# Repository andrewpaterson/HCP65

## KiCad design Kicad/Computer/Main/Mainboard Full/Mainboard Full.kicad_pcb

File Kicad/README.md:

# Kicad

The HCP65's circuit boards, drawn in KiCad 8, and the libraries they are drawn with.  The schematics are a source
of the website's hardware pages (`HCP65-Emulator/HCP65Lib/Docs/hcp65`): what a page says about a board is made from
or checked against its schematic (`Website/DocsPlan.txt` I).

| Folder | Has |
|---|---|
| `Computer` | The computer's boards, by what they do: Main, Memory, Audio, Video, the device boards, and `Component Boards`, the small boards the others are built from. |
| `Boards` | Blank boards (`Blank`) and pin boards (`Pins`) of each size of socket, to start a board from. |
| `Pico`, `Programmers`, `Tester`, `Speed`, `Keypad` | Test, programming and other boards beside the computer. |
| `X65C64` | The 65C64 drawn as a part: its schematic and board. |
| `Old` | Boards no longer built, kept to look back at. |
| `Symbols`, `HCP65_Parts.pretty` | The symbol libraries (one a maker, and `HCP65.kicad_sym`, a symbol a board) and the footprints of the boards and sockets. |
| `SamacSys_Parts.pretty`, `SamacSys_Parts.3dshapes` | Footprints and 3D models of bought parts. |

A board's `<board> Faults.txt` (and `Symbols/Symbol Faults.txt`) lists what a review found wrong with it.  Export
from a copy of a project, not the project itself: `kicad-cli` rewrites the `.kicad_prl` beside every schematic it
reads.

| Files | Are | From |
|---|---|---|
| `**/*.kicad_sch`, `**/*.kicad_pcb`, `**/*.kicad_pro`, `*.kicad_wks`, `**/*.round-tracks-config`, `**/*.par`, `**/*.frb`, `**/sym-lib-table`, `Old/**/*.sch`, `Old/**/*.pro`, `Old/**/*.dcm` | Source | Drawn in KiCad 8 (`Old`'s `.sch`, `.pro` and `.dcm` in KiCad 5); the round tracks plugin's settings and Freerouting's files. |
| `**/*.txt` | Source | Notes: each review's faults, pin lists. |
| `Symbols/*.kicad_sym`, `HCP65_Parts.pretty/*.kicad_mod` | Source | Drawn and kept here (the makers' symbols were begun from SamacSys's, and corrected as `Symbols/Symbol Faults.txt` says). |
| `SamacSys_Parts.pretty/*.kicad_mod`, `SamacSys_Parts.3dshapes/*` | Third-party | SamacSys's Component Search Engine: each part's footprint and 3D model as its Library Loader downloaded it. |
| `**/*.g[bt][losp]`, `**/*.gm1`, `**/*.gbr`, `**/*.gbrjob`, `**/*.drl` | Generated | A board's Gerber and drill files, plotted from its `.kicad_pcb` by KiCad 8's Pcbnew (File, Fabrication Outputs: Gerbers, then Drill Files; `kicad-cli pcb export gerbers` and `kicad-cli pcb export drill` make the same) into a folder named for the board beside it. |
| `Boards/**/*.wrl`, `Computer/**/*.wrl`, `Old/**/*.wrl`, `Pico/**/*.wrl`, `Tester/**/*.wrl` | Generated | A board's 3D model, exported from its `.kicad_pcb` by Pcbnew (File, Export, VRML; `kicad-cli pcb export vrml`). |
| `Old/**/*.step` | Generated | A board's 3D model, exported from its `.kicad_pcb` by Pcbnew (File, Export, STEP; `kicad-cli pcb export step`). |
| `**/*.cad` | Generated | A board in GenCAD, exported from its `.kicad_pcb` by Pcbnew (File, Export, GenCAD). |
| `Old/**/*.net` | Generated | A schematic's netlist, exported by Eeschema (File, Export, Netlist; `kicad-cli sch export netlist`). |
| `Keypad/Fabrication/*.7z` | Generated | The Keypad's Gerber and drill files beside it, packed to send to the board maker. |

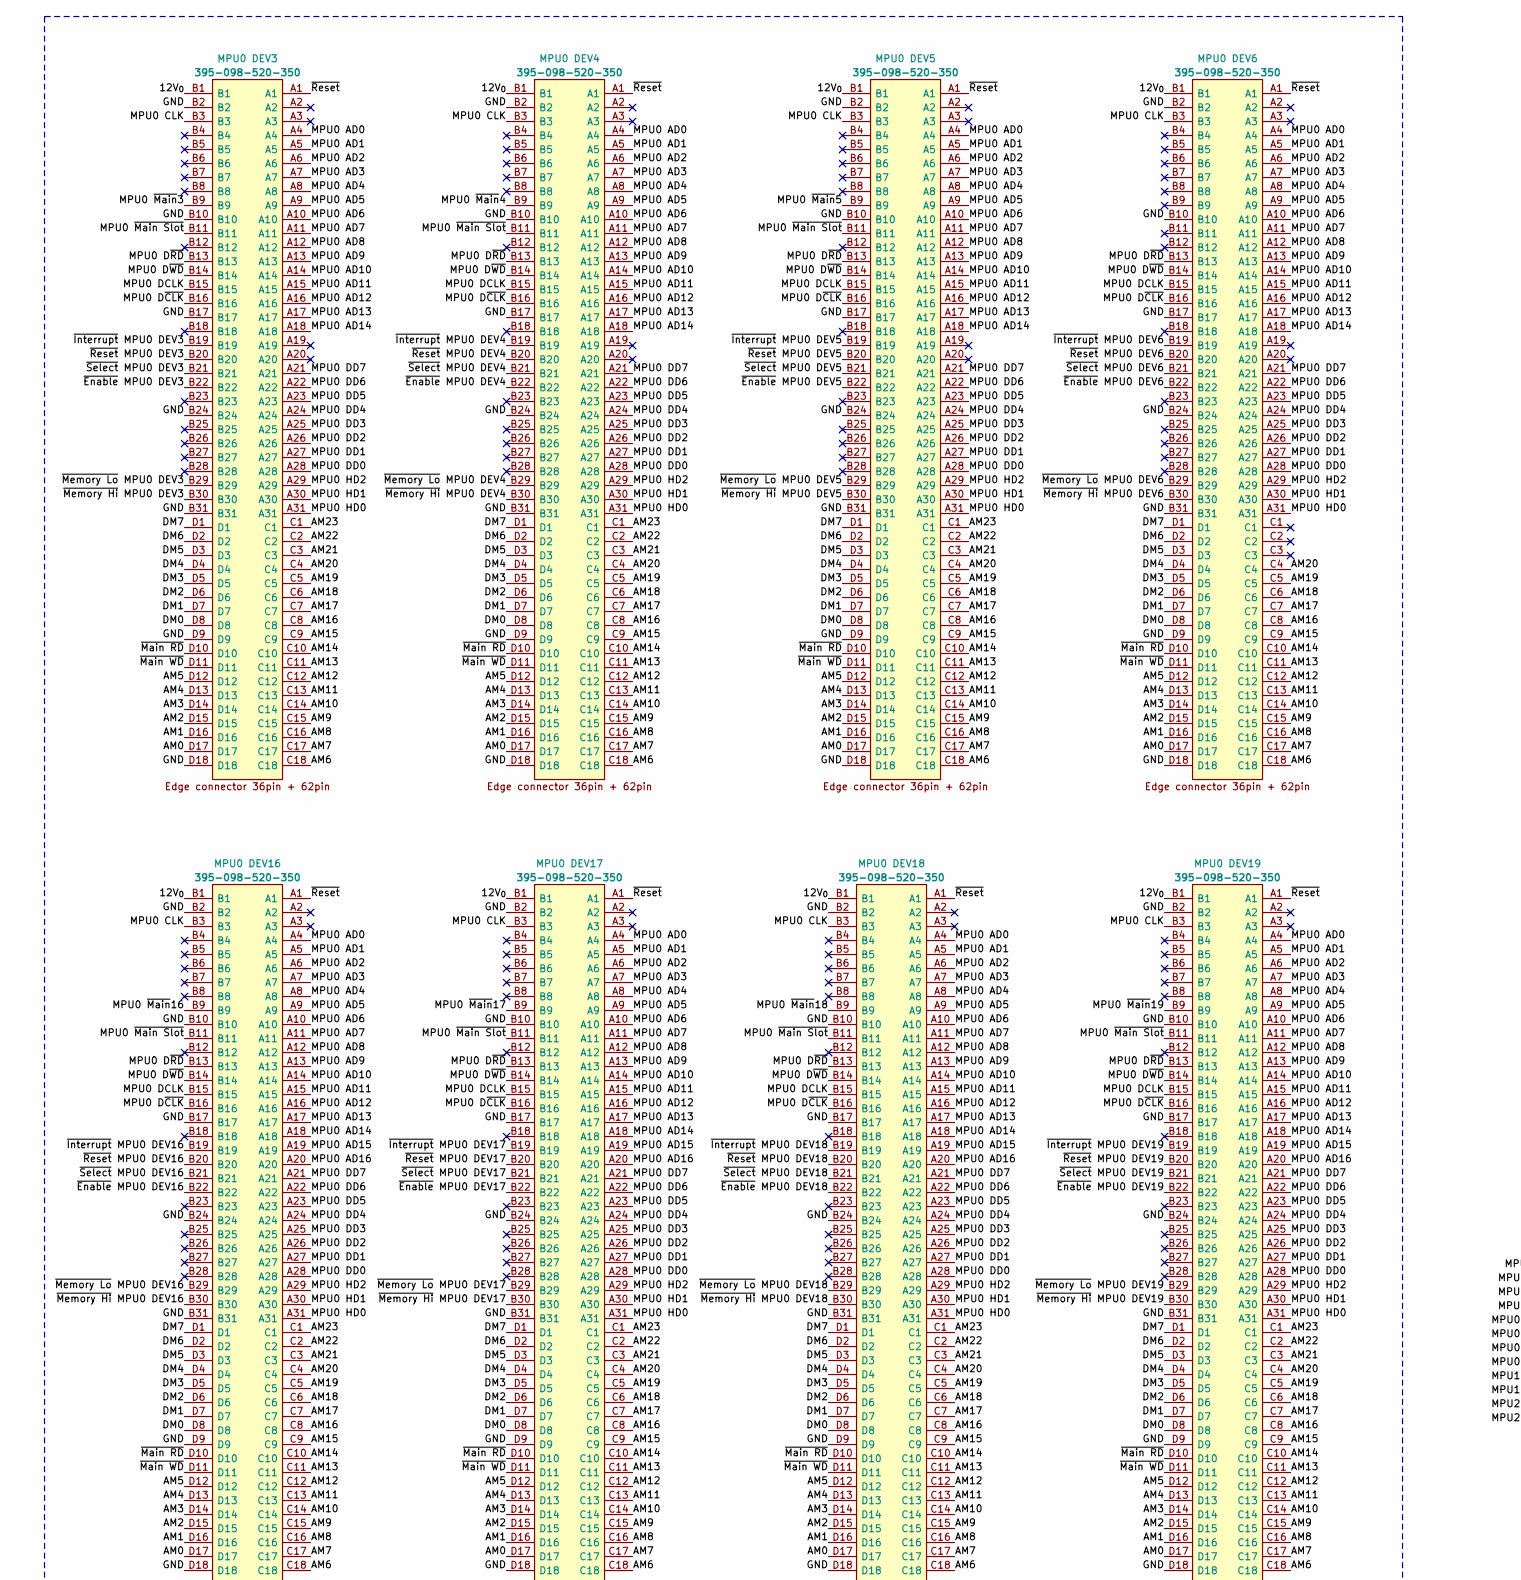
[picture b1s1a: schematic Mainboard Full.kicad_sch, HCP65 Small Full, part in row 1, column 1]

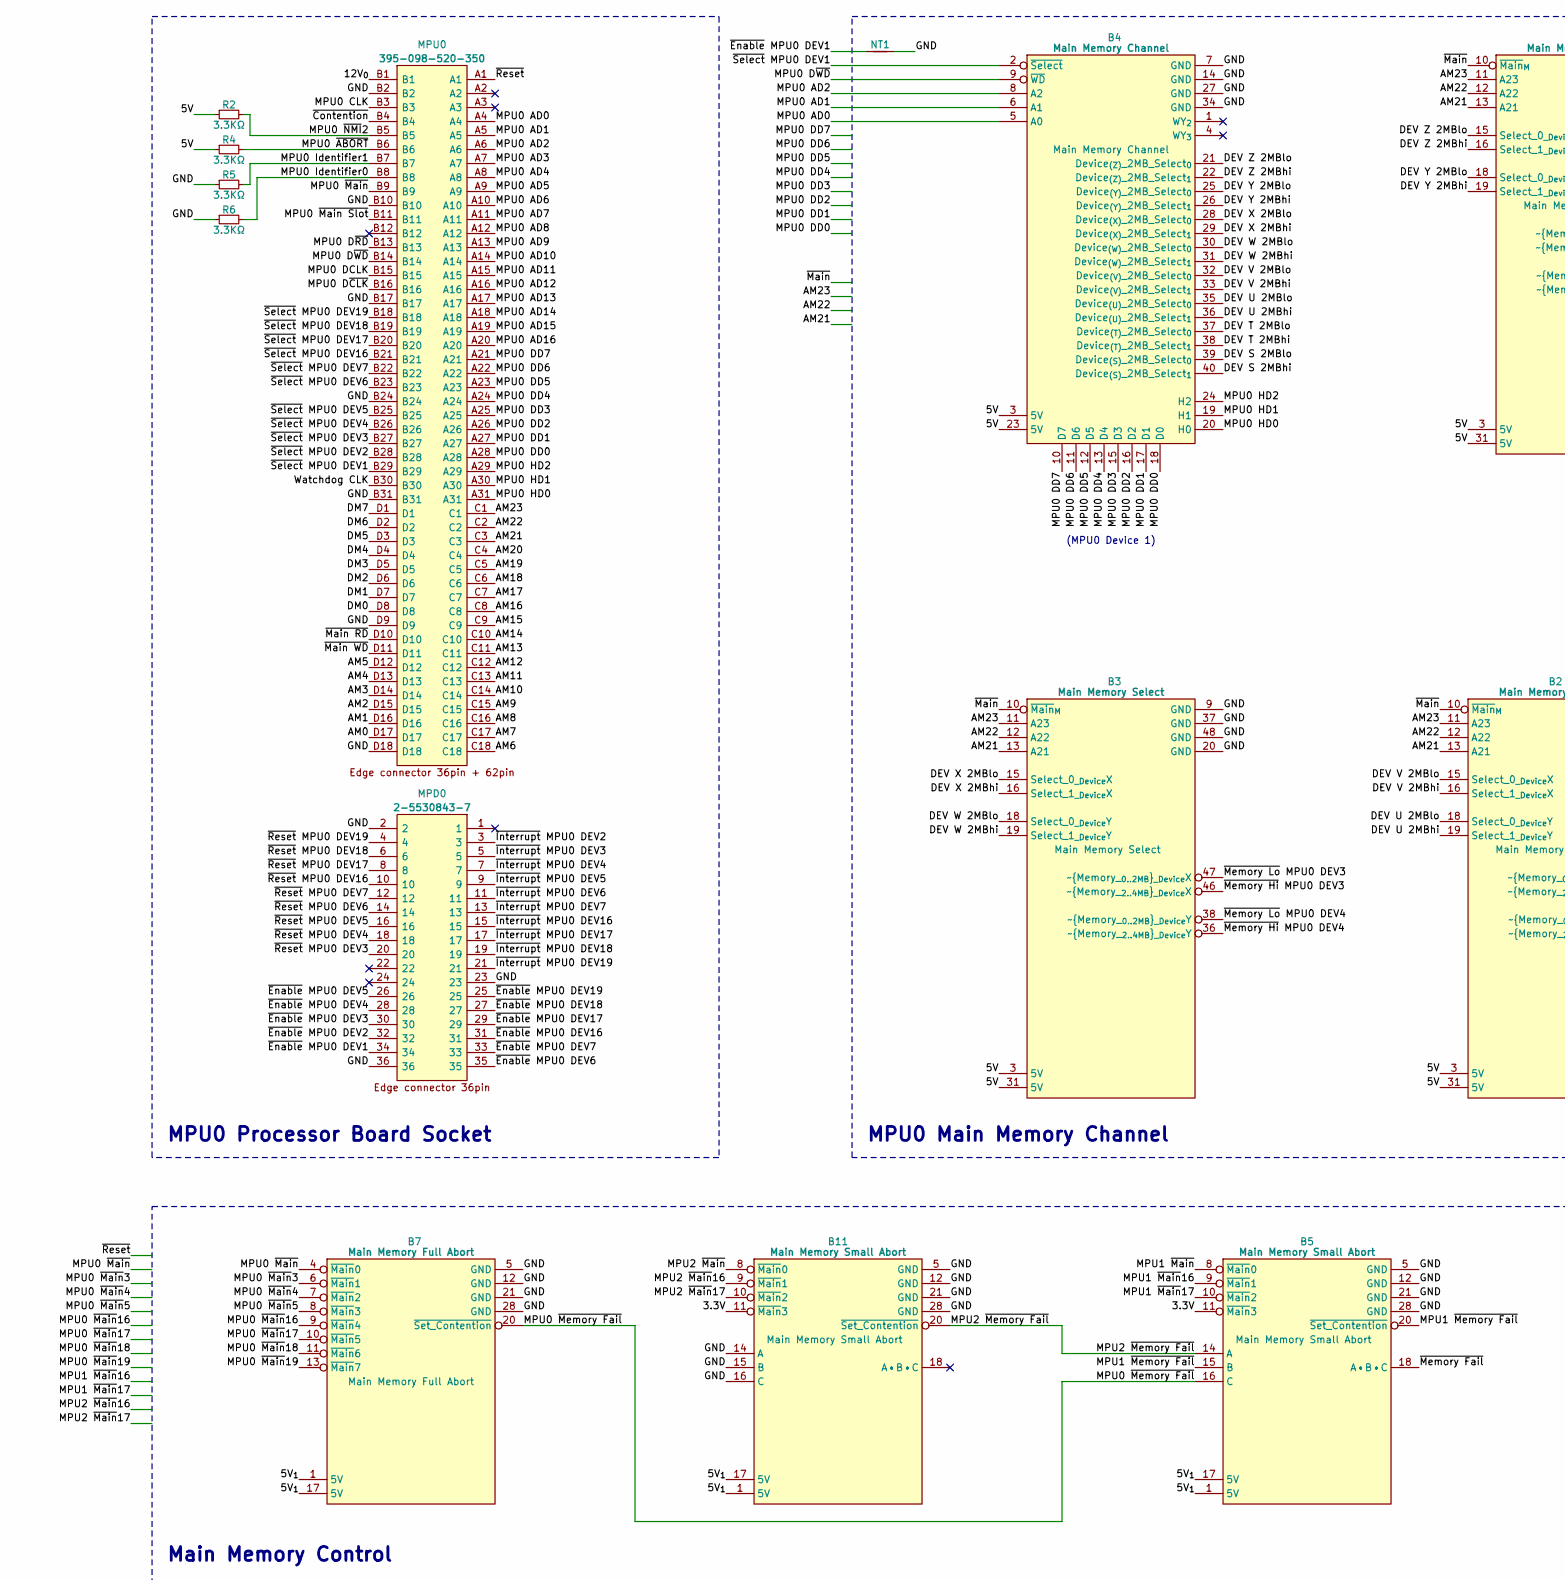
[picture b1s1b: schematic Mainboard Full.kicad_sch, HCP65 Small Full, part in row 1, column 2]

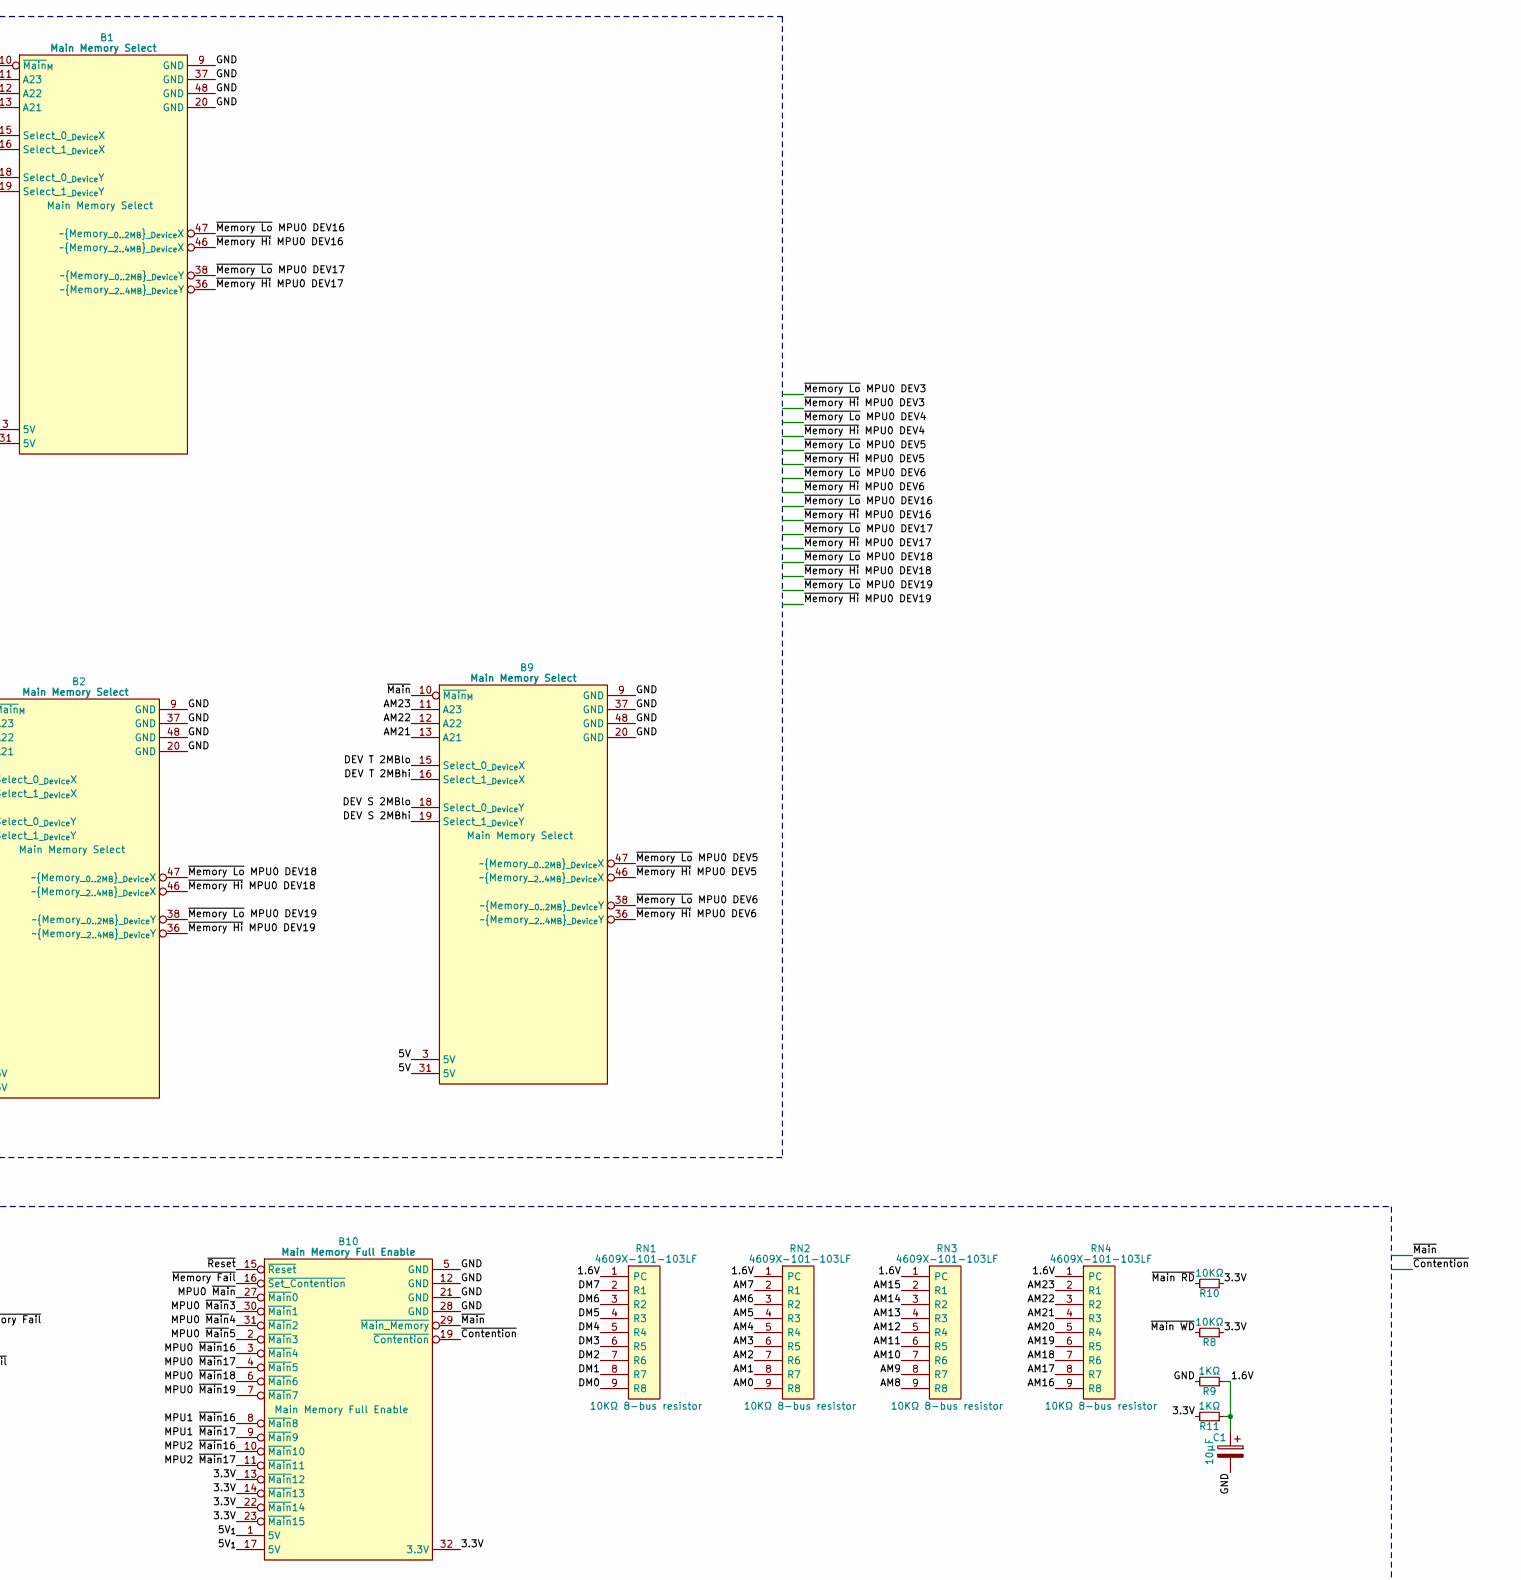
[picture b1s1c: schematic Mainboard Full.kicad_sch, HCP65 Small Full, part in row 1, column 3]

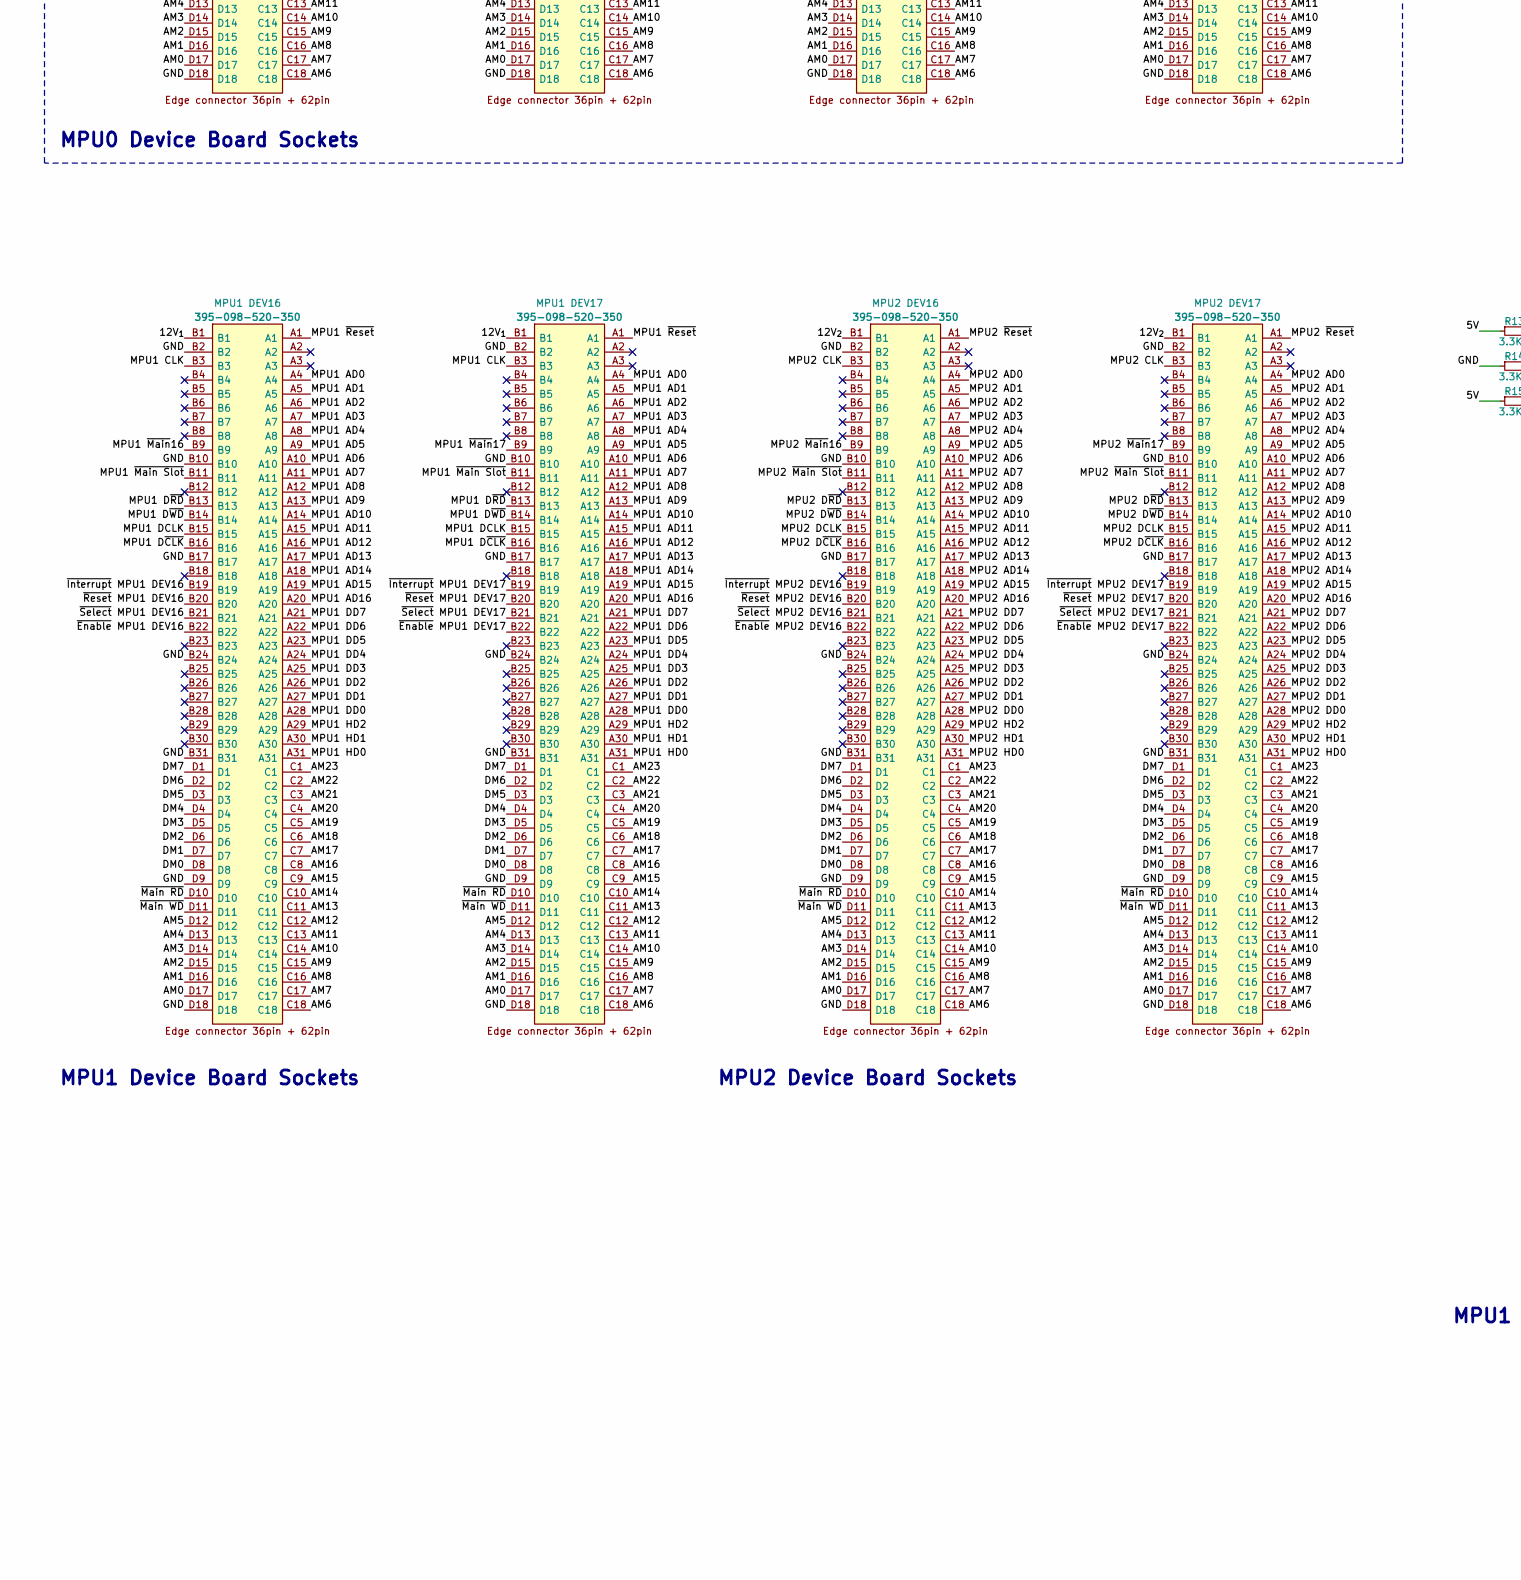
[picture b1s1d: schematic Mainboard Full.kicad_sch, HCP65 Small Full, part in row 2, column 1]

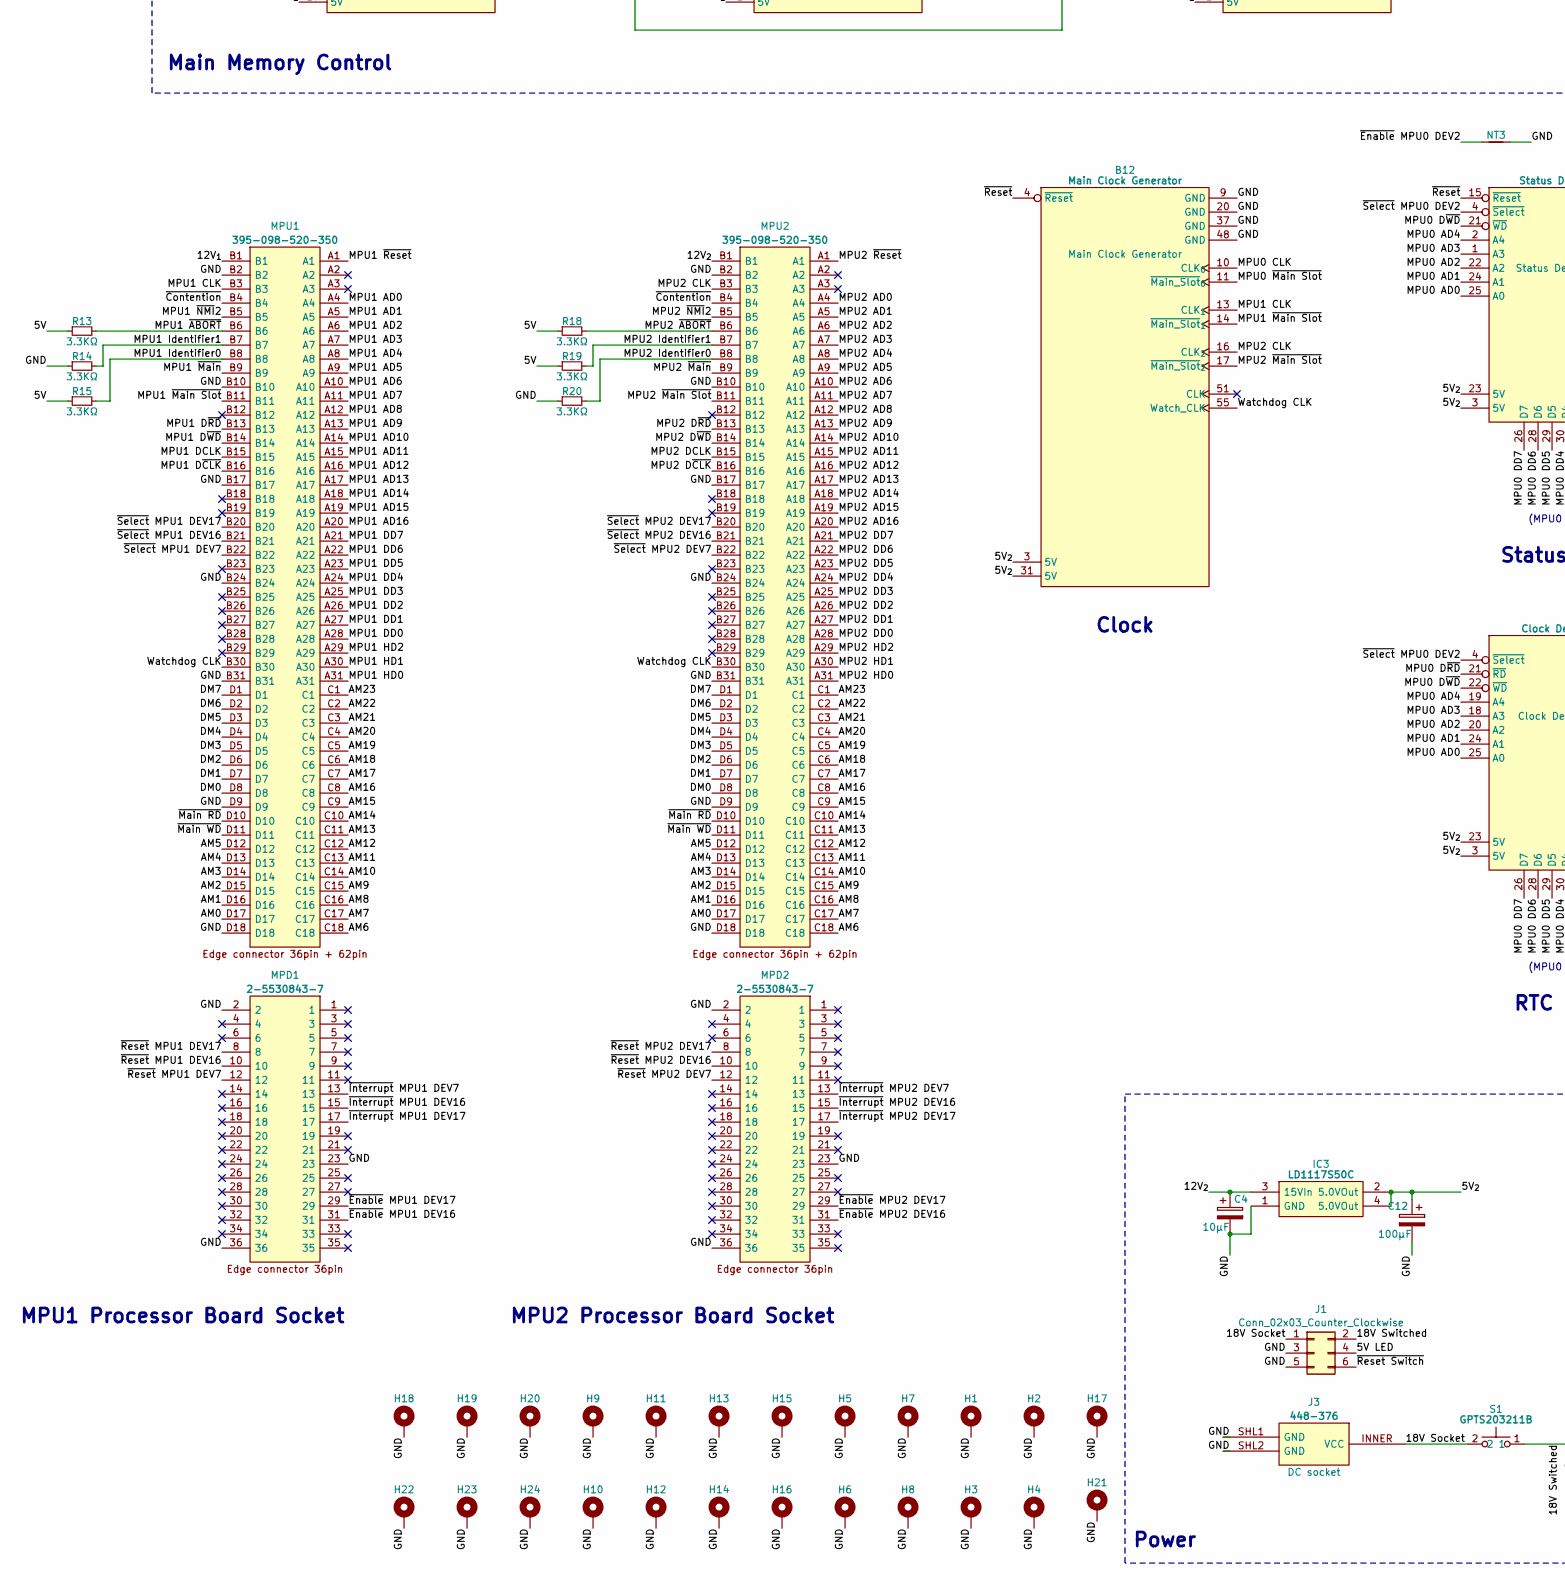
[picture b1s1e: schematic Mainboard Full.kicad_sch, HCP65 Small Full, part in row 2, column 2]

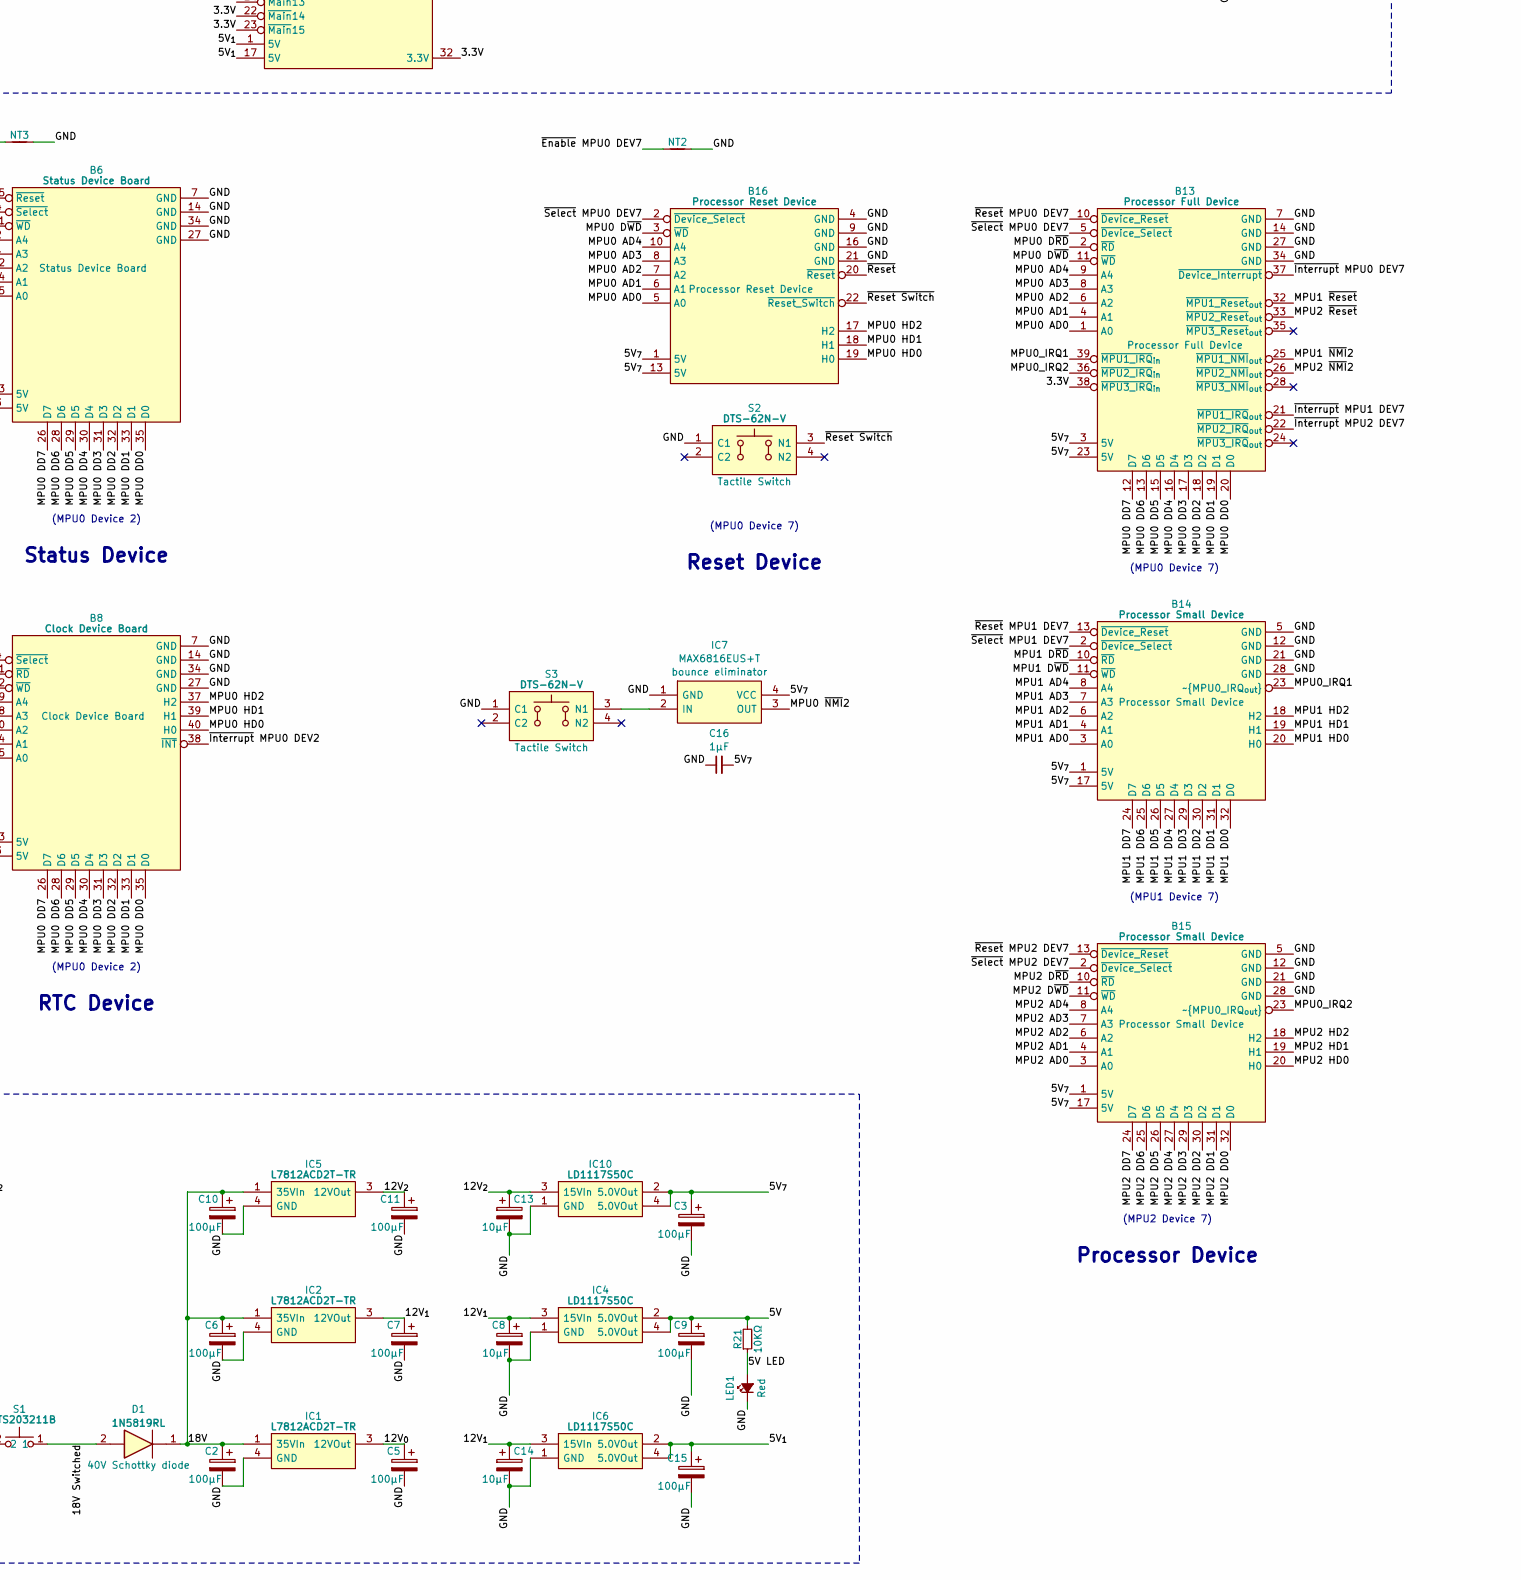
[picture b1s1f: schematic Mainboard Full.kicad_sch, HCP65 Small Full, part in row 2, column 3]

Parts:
B1, B2, B3, B9: Main Memory Select; HCP65_Main_Memory_Select
B4: Main Memory Channel; HCP65_Main_Memory_Channel
B5, B11: Main Memory Small Abort; HCP65_Main_Memory_Small_Abort
B6: Status Device Board; HCP65_Status_Device_Board
B7: Main Memory Full Abort; HCP65_Main_Memory_Full_Abort
B8: Clock Device Board; HCP65_Clock_Device_Board
B10: Main Memory Full Enable; HCP65_Main_Memory_Full_Enable
B12: Main Clock Generator; HCP65_Clock_Generator
B13: Processor Full Device; HCP65_Processor_Full_Device
B14, B15: Processor Small Device; HCP65_Processor_Small_Device
B16: Processor Reset Device; HCP65_Processor_Reset_Device
C1, C4, C8, C13, C14: 10μF; CP_Radial_D4.0mm_P2.00mm
C2, C3, C5, C6, C7, C9, C10, C11, C12, C15: 100μF; CP_Radial_D6.3mm_P2.50mm
C16: 1μF; C_0805
D1: 1N5819RL; DIOAD1414W86L464D238; Manufacturer_Part_Number 1N5819RL; Mouser Part Number 511-1N5819-TR
H1, H2, H3, H4, H5, H6, H7, H8, H9, H10, H11, H12, H13, H14, H15, H16, H17, H18, H19, H20, H21, H22, H23, H24: MountingHole_Pad; HCP65_MountingHole_M3_
IC1, IC2, IC5: L7812ACD2T-TR; TO254P1542X460-3N; Manufacturer_Part_Number L7812ACD2T-TR
IC3, IC4, IC6, IC10: LD1117S50C; LD1117S33C; Manufacturer_Part_Number LD1117S50C
IC7: MAX6816EUS+T; MAX812REUST; Manufacturer_Part_Number MAX6816EUS+T; Mouser Part Number 700-MAX6816EUST
J1: Conn_02x03_Counter_Clockwise; PinHeader_2x03_P2.54mm_Vertical
J3: 448-376; 448376; Manufacturer_Part_Number 448-376
LED1: Red; LED_D5.0mm
MPD0, MPD1, MPD2: 2-5530843-7; 255308437; Manufacturer_Part_Number 2-5530843-7; Mouser Part Number 571-2-5530843-7
MPU0, MPU0 DEV3, MPU0 DEV4, MPU0 DEV5, MPU0 DEV6, MPU0 DEV16, MPU0 DEV17, MPU0 DEV18, MPU0 DEV19, MPU1, MPU1 DEV16, MPU1 DEV17, MPU2, MPU2 DEV16, MPU2 DEV17: 395-098-520-350; 395098520350; Manufacturer_Part_Number 395-098-520-350; Mouser Part Number 587-395-098-520-350
NT1, NT2, NT3: NetTie; NetTie-2_SMD_Pad0.5mm
R2, R4, R5, R6, R13, R14, R15, R18, R19, R20: 3.3KΩ; R_0805
R8, R10, R21: 10KΩ; R_0805
R9, R11: 1KΩ; R_0805
RN1, RN2, RN3, RN4: 4609X-101-103LF; 4609X
S1: GPTS203211B; Manufacturer_Part_Number GPTS203211B; Mouser Part Number 629-GPTS203211B
S2, S3: DTS-62N-V; DTS62NV; Manufacturer_Part_Number DTS-62N-V; Mouser Part Number 113-DTS-62N-V

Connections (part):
/1.6V: C1.1, R9.1, R11.1, RN1.1 (PC), RN2.1 (PC), RN3.1 (PC), RN4.1 (PC)
/3.3V: B5.11 (~Main3), B10.13 (~Main12), B10.14 (~Main13), B10.22 (~Main14), B10.23 (~Main15), B10.32 (3.3V), B11.11 (~Main3), B13.38 (~MPU3_IRQ_{in}), R8.1, R10.1, R11.2
/5V: B1.3 (5V), B1.31 (5V), B2.3 (5V), B2.31 (5V), B3.3 (5V), B3.31 (5V), B4.3 (5V), B4.23 (5V), B9.3 (5V), B9.31 (5V), C9.1, IC4.2 (5.0VOut), IC4.4 (5.0VOut), R2.1, R4.1, R13.1, R15.1, R18.1, R19.1, R21.2
/5V LED: J1.4, LED1.2 (A), R21.1
/5V_{1}: B5.1 (5V), B5.17 (5V), B7.1 (5V), B7.17 (5V), B10.1 (5V), B10.17 (5V), B11.1 (5V), B11.17 (5V), C15.1, IC6.2 (5.0VOut), IC6.4 (5.0VOut)
/5V_{2}: B6.3 (5V), B6.23 (5V), B8.3 (5V), B8.23 (5V), B12.3 (5V), B12.31 (5V), C12.1, IC3.2 (5.0VOut), IC3.4 (5.0VOut)
/5V_{7}: B13.3 (5V), B13.23 (5V), B14.1 (5V), B14.17 (5V), B15.1 (5V), B15.17 (5V), B16.1 (5V), B16.13 (5V), C3.1, C16.2, IC7.4 (VCC), IC10.2 (5.0VOut), IC10.4 (5.0VOut)
/12V_{0}: C5.1, IC1.3 (12VOut), MPU0.B1, MPU0 DEV3.B1, MPU0 DEV4.B1, MPU0 DEV5.B1, MPU0 DEV6.B1, MPU0 DEV16.B1, MPU0 DEV17.B1, MPU0 DEV18.B1, MPU0 DEV19.B1
/12V_{1}: C7.1, C8.1, C14.1, IC2.3 (12VOut), IC4.3 (15VIn), IC6.3 (15VIn), MPU1.B1, MPU1 DEV16.B1, MPU1 DEV17.B1
/12V_{2}: C4.1, C11.1, C13.1, IC3.3 (15VIn), IC5.3 (12VOut), IC10.3 (15VIn), MPU2.B1, MPU2 DEV16.B1, MPU2 DEV17.B1
/18V: C2.1, C6.1, C10.1, D1.1, IC1.1 (35VIn), IC2.1 (35VIn), IC5.1 (35VIn)
/18V Socket: J1.1, J3.INNER (VCC), S1.2
/18V Switched: D1.2, J1.2, S1.1
/AM0: MPU0.D17, MPU0 DEV3.D17, MPU0 DEV4.D17, MPU0 DEV5.D17, MPU0 DEV6.D17, MPU0 DEV16.D17, MPU0 DEV17.D17, MPU0 DEV18.D17, MPU0 DEV19.D17, MPU1.D17, MPU1 DEV16.D17, MPU1 DEV17.D17, MPU2.D17, MPU2 DEV16.D17, MPU2 DEV17.D17, RN2.9 (R8)
/AM1: MPU0.D16, MPU0 DEV3.D16, MPU0 DEV4.D16, MPU0 DEV5.D16, MPU0 DEV6.D16, MPU0 DEV16.D16, MPU0 DEV17.D16, MPU0 DEV18.D16, MPU0 DEV19.D16, MPU1.D16, MPU1 DEV16.D16, MPU1 DEV17.D16, MPU2.D16, MPU2 DEV16.D16, MPU2 DEV17.D16, RN2.8 (R7)
/AM2: MPU0.D15, MPU0 DEV3.D15, MPU0 DEV4.D15, MPU0 DEV5.D15, MPU0 DEV6.D15, MPU0 DEV16.D15, MPU0 DEV17.D15, MPU0 DEV18.D15, MPU0 DEV19.D15, MPU1.D15, MPU1 DEV16.D15, MPU1 DEV17.D15, MPU2.D15, MPU2 DEV16.D15, MPU2 DEV17.D15, RN2.7 (R6)
/AM3: MPU0.D14, MPU0 DEV3.D14, MPU0 DEV4.D14, MPU0 DEV5.D14, MPU0 DEV6.D14, MPU0 DEV16.D14, MPU0 DEV17.D14, MPU0 DEV18.D14, MPU0 DEV19.D14, MPU1.D14, MPU1 DEV16.D14, MPU1 DEV17.D14, MPU2.D14, MPU2 DEV16.D14, MPU2 DEV17.D14, RN2.6 (R5)
/AM4: MPU0.D13, MPU0 DEV3.D13, MPU0 DEV4.D13, MPU0 DEV5.D13, MPU0 DEV6.D13, MPU0 DEV16.D13, MPU0 DEV17.D13, MPU0 DEV18.D13, MPU0 DEV19.D13, MPU1.D13, MPU1 DEV16.D13, MPU1 DEV17.D13, MPU2.D13, MPU2 DEV16.D13, MPU2 DEV17.D13, RN2.5 (R4)
/AM5: MPU0.D12, MPU0 DEV3.D12, MPU0 DEV4.D12, MPU0 DEV5.D12, MPU0 DEV6.D12, MPU0 DEV16.D12, MPU0 DEV17.D12, MPU0 DEV18.D12, MPU0 DEV19.D12, MPU1.D12, MPU1 DEV16.D12, MPU1 DEV17.D12, MPU2.D12, MPU2 DEV16.D12, MPU2 DEV17.D12, RN2.4 (R3)
/AM6: MPU0.C18, MPU0 DEV3.C18, MPU0 DEV4.C18, MPU0 DEV5.C18, MPU0 DEV6.C18, MPU0 DEV16.C18, MPU0 DEV17.C18, MPU0 DEV18.C18, MPU0 DEV19.C18, MPU1.C18, MPU1 DEV16.C18, MPU1 DEV17.C18, MPU2.C18, MPU2 DEV16.C18, MPU2 DEV17.C18, RN2.3 (R2)
/AM7: MPU0.C17, MPU0 DEV3.C17, MPU0 DEV4.C17, MPU0 DEV5.C17, MPU0 DEV6.C17, MPU0 DEV16.C17, MPU0 DEV17.C17, MPU0 DEV18.C17, MPU0 DEV19.C17, MPU1.C17, MPU1 DEV16.C17, MPU1 DEV17.C17, MPU2.C17, MPU2 DEV16.C17, MPU2 DEV17.C17, RN2.2 (R1)
/AM8: MPU0.C16, MPU0 DEV3.C16, MPU0 DEV4.C16, MPU0 DEV5.C16, MPU0 DEV6.C16, MPU0 DEV16.C16, MPU0 DEV17.C16, MPU0 DEV18.C16, MPU0 DEV19.C16, MPU1.C16, MPU1 DEV16.C16, MPU1 DEV17.C16, MPU2.C16, MPU2 DEV16.C16, MPU2 DEV17.C16, RN3.9 (R8)
/AM9: MPU0.C15, MPU0 DEV3.C15, MPU0 DEV4.C15, MPU0 DEV5.C15, MPU0 DEV6.C15, MPU0 DEV16.C15, MPU0 DEV17.C15, MPU0 DEV18.C15, MPU0 DEV19.C15, MPU1.C15, MPU1 DEV16.C15, MPU1 DEV17.C15, MPU2.C15, MPU2 DEV16.C15, MPU2 DEV17.C15, RN3.8 (R7)
/AM10: MPU0.C14, MPU0 DEV3.C14, MPU0 DEV4.C14, MPU0 DEV5.C14, MPU0 DEV6.C14, MPU0 DEV16.C14, MPU0 DEV17.C14, MPU0 DEV18.C14, MPU0 DEV19.C14, MPU1.C14, MPU1 DEV16.C14, MPU1 DEV17.C14, MPU2.C14, MPU2 DEV16.C14, MPU2 DEV17.C14, RN3.7 (R6)
/AM11: MPU0.C13, MPU0 DEV3.C13, MPU0 DEV4.C13, MPU0 DEV5.C13, MPU0 DEV6.C13, MPU0 DEV16.C13, MPU0 DEV17.C13, MPU0 DEV18.C13, MPU0 DEV19.C13, MPU1.C13, MPU1 DEV16.C13, MPU1 DEV17.C13, MPU2.C13, MPU2 DEV16.C13, MPU2 DEV17.C13, RN3.6 (R5)
/AM12: MPU0.C12, MPU0 DEV3.C12, MPU0 DEV4.C12, MPU0 DEV5.C12, MPU0 DEV6.C12, MPU0 DEV16.C12, MPU0 DEV17.C12, MPU0 DEV18.C12, MPU0 DEV19.C12, MPU1.C12, MPU1 DEV16.C12, MPU1 DEV17.C12, MPU2.C12, MPU2 DEV16.C12, MPU2 DEV17.C12, RN3.5 (R4)
/AM13: MPU0.C11, MPU0 DEV3.C11, MPU0 DEV4.C11, MPU0 DEV5.C11, MPU0 DEV6.C11, MPU0 DEV16.C11, MPU0 DEV17.C11, MPU0 DEV18.C11, MPU0 DEV19.C11, MPU1.C11, MPU1 DEV16.C11, MPU1 DEV17.C11, MPU2.C11, MPU2 DEV16.C11, MPU2 DEV17.C11, RN3.4 (R3)
/AM14: MPU0.C10, MPU0 DEV3.C10, MPU0 DEV4.C10, MPU0 DEV5.C10, MPU0 DEV6.C10, MPU0 DEV16.C10, MPU0 DEV17.C10, MPU0 DEV18.C10, MPU0 DEV19.C10, MPU1.C10, MPU1 DEV16.C10, MPU1 DEV17.C10, MPU2.C10, MPU2 DEV16.C10, MPU2 DEV17.C10, RN3.3 (R2)
/AM15: MPU0.C9, MPU0 DEV3.C9, MPU0 DEV4.C9, MPU0 DEV5.C9, MPU0 DEV6.C9, MPU0 DEV16.C9, MPU0 DEV17.C9, MPU0 DEV18.C9, MPU0 DEV19.C9, MPU1.C9, MPU1 DEV16.C9, MPU1 DEV17.C9, MPU2.C9, MPU2 DEV16.C9, MPU2 DEV17.C9, RN3.2 (R1)
/AM16: MPU0.C8, MPU0 DEV3.C8, MPU0 DEV4.C8, MPU0 DEV5.C8, MPU0 DEV6.C8, MPU0 DEV16.C8, MPU0 DEV17.C8, MPU0 DEV18.C8, MPU0 DEV19.C8, MPU1.C8, MPU1 DEV16.C8, MPU1 DEV17.C8, MPU2.C8, MPU2 DEV16.C8, MPU2 DEV17.C8, RN4.9 (R8)
/AM17: MPU0.C7, MPU0 DEV3.C7, MPU0 DEV4.C7, MPU0 DEV5.C7, MPU0 DEV6.C7, MPU0 DEV16.C7, MPU0 DEV17.C7, MPU0 DEV18.C7, MPU0 DEV19.C7, MPU1.C7, MPU1 DEV16.C7, MPU1 DEV17.C7, MPU2.C7, MPU2 DEV16.C7, MPU2 DEV17.C7, RN4.8 (R7)
/AM18: MPU0.C6, MPU0 DEV3.C6, MPU0 DEV4.C6, MPU0 DEV5.C6, MPU0 DEV6.C6, MPU0 DEV16.C6, MPU0 DEV17.C6, MPU0 DEV18.C6, MPU0 DEV19.C6, MPU1.C6, MPU1 DEV16.C6, MPU1 DEV17.C6, MPU2.C6, MPU2 DEV16.C6, MPU2 DEV17.C6, RN4.7 (R6)
/AM19: MPU0.C5, MPU0 DEV3.C5, MPU0 DEV4.C5, MPU0 DEV5.C5, MPU0 DEV6.C5, MPU0 DEV16.C5, MPU0 DEV17.C5, MPU0 DEV18.C5, MPU0 DEV19.C5, MPU1.C5, MPU1 DEV16.C5, MPU1 DEV17.C5, MPU2.C5, MPU2 DEV16.C5, MPU2 DEV17.C5, RN4.6 (R5)
/AM20: MPU0.C4, MPU0 DEV3.C4, MPU0 DEV4.C4, MPU0 DEV5.C4, MPU0 DEV6.C4, MPU0 DEV16.C4, MPU0 DEV17.C4, MPU0 DEV18.C4, MPU0 DEV19.C4, MPU1.C4, MPU1 DEV16.C4, MPU1 DEV17.C4, MPU2.C4, MPU2 DEV16.C4, MPU2 DEV17.C4, RN4.5 (R4)
/AM21: B1.13 (A21), B2.13 (A21), B3.13 (A21), B9.13 (A21), MPU0.C3, MPU0 DEV3.C3, MPU0 DEV4.C3, MPU0 DEV5.C3, MPU0 DEV16.C3, MPU0 DEV17.C3, MPU0 DEV18.C3, MPU0 DEV19.C3, MPU1.C3, MPU1 DEV16.C3, MPU1 DEV17.C3, MPU2.C3, MPU2 DEV16.C3, MPU2 DEV17.C3, RN4.4 (R3)
/AM22: B1.12 (A22), B2.12 (A22), B3.12 (A22), B9.12 (A22), MPU0.C2, MPU0 DEV3.C2, MPU0 DEV4.C2, MPU0 DEV5.C2, MPU0 DEV16.C2, MPU0 DEV17.C2, MPU0 DEV18.C2, MPU0 DEV19.C2, MPU1.C2, MPU1 DEV16.C2, MPU1 DEV17.C2, MPU2.C2, MPU2 DEV16.C2, MPU2 DEV17.C2, RN4.3 (R2)
/AM23: B1.11 (A23), B2.11 (A23), B3.11 (A23), B9.11 (A23), MPU0.C1, MPU0 DEV3.C1, MPU0 DEV4.C1, MPU0 DEV5.C1, MPU0 DEV16.C1, MPU0 DEV17.C1, MPU0 DEV18.C1, MPU0 DEV19.C1, MPU1.C1, MPU1 DEV16.C1, MPU1 DEV17.C1, MPU2.C1, MPU2 DEV16.C1, MPU2 DEV17.C1, RN4.2 (R1)
/DEV S 2MBhi: B4.40 (Device_{(S)}_2MB_Select_{1}), B9.19 (Select_1_{_Device}Y)
/DEV S 2MBlo: B4.39 (Device_{(S)}_2MB_Select_{0}), B9.18 (Select_0_{_Device}Y)
/DEV T 2MBhi: B4.38 (Device_{(T)}_2MB_Select_{1}), B9.16 (Select_1_{_Device}X)
/DEV T 2MBlo: B4.37 (Device_{(T)}_2MB_Select_{0}), B9.15 (Select_0_{_Device}X)
/DEV U 2MBhi: B2.19 (Select_1_{_Device}Y), B4.36 (Device_{(U)}_2MB_Select_{1})
/DEV U 2MBlo: B2.18 (Select_0_{_Device}Y), B4.35 (Device_{(U)}_2MB_Select_{0})
/DEV V 2MBhi: B2.16 (Select_1_{_Device}X), B4.33 (Device_{(V)}_2MB_Select_{1})
/DEV V 2MBlo: B2.15 (Select_0_{_Device}X), B4.32 (Device_{(V)}_2MB_Select_{0})
/DEV W 2MBhi: B3.19 (Select_1_{_Device}Y), B4.31 (Device_{(W)}_2MB_Select_{1})
/DEV W 2MBlo: B3.18 (Select_0_{_Device}Y), B4.30 (Device_{(W)}_2MB_Select_{0})
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
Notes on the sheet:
RTC Device
Clock
MPU2 Device Board Sockets
MPU1 Device Board Sockets
Processor Device
(MPU0 Device 1)
MPU0 Processor Board Socket
Power
Main Memory Control
(MPU0 Device 2)
(MPU0 Device 7)
MPU2 Processor Board Socket
MPU0 Main Memory Channel
Status Device
MPU1 Processor Board Socket
(MPU1 Device 7)
MPU0 Device Board Sockets
(MPU2 Device 7)
Reset Device

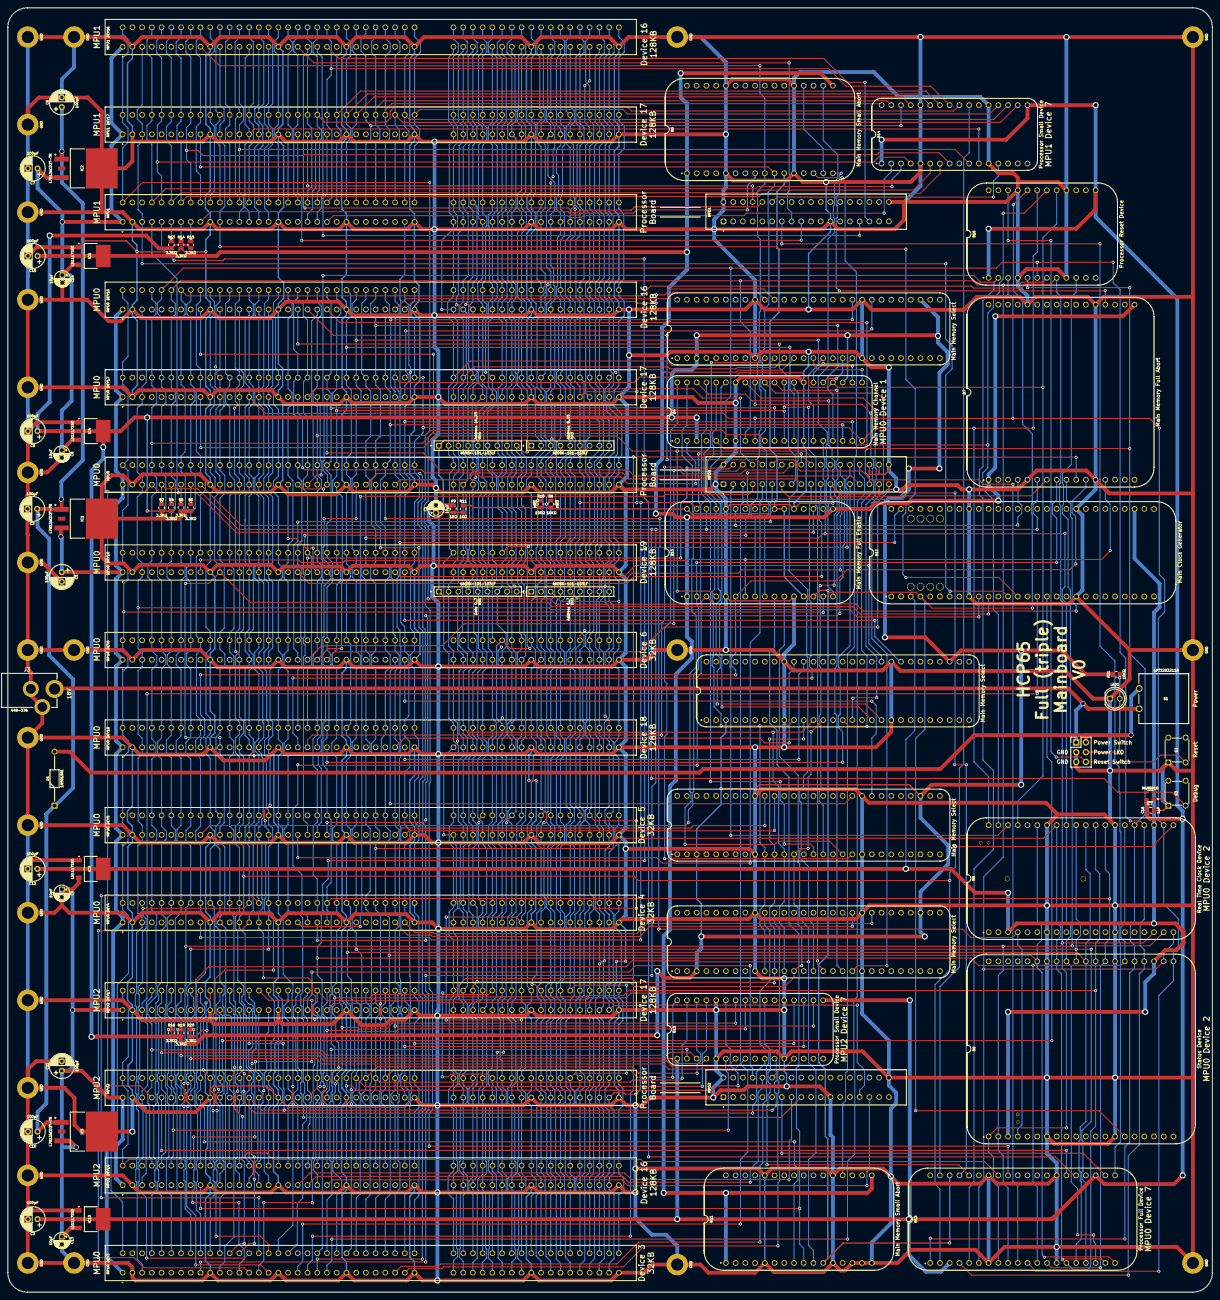
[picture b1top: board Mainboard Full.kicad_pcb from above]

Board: 2 copper layers, 314.5 x 335.3 mm, 111 parts (0 on the bottom side), 285 nets.
